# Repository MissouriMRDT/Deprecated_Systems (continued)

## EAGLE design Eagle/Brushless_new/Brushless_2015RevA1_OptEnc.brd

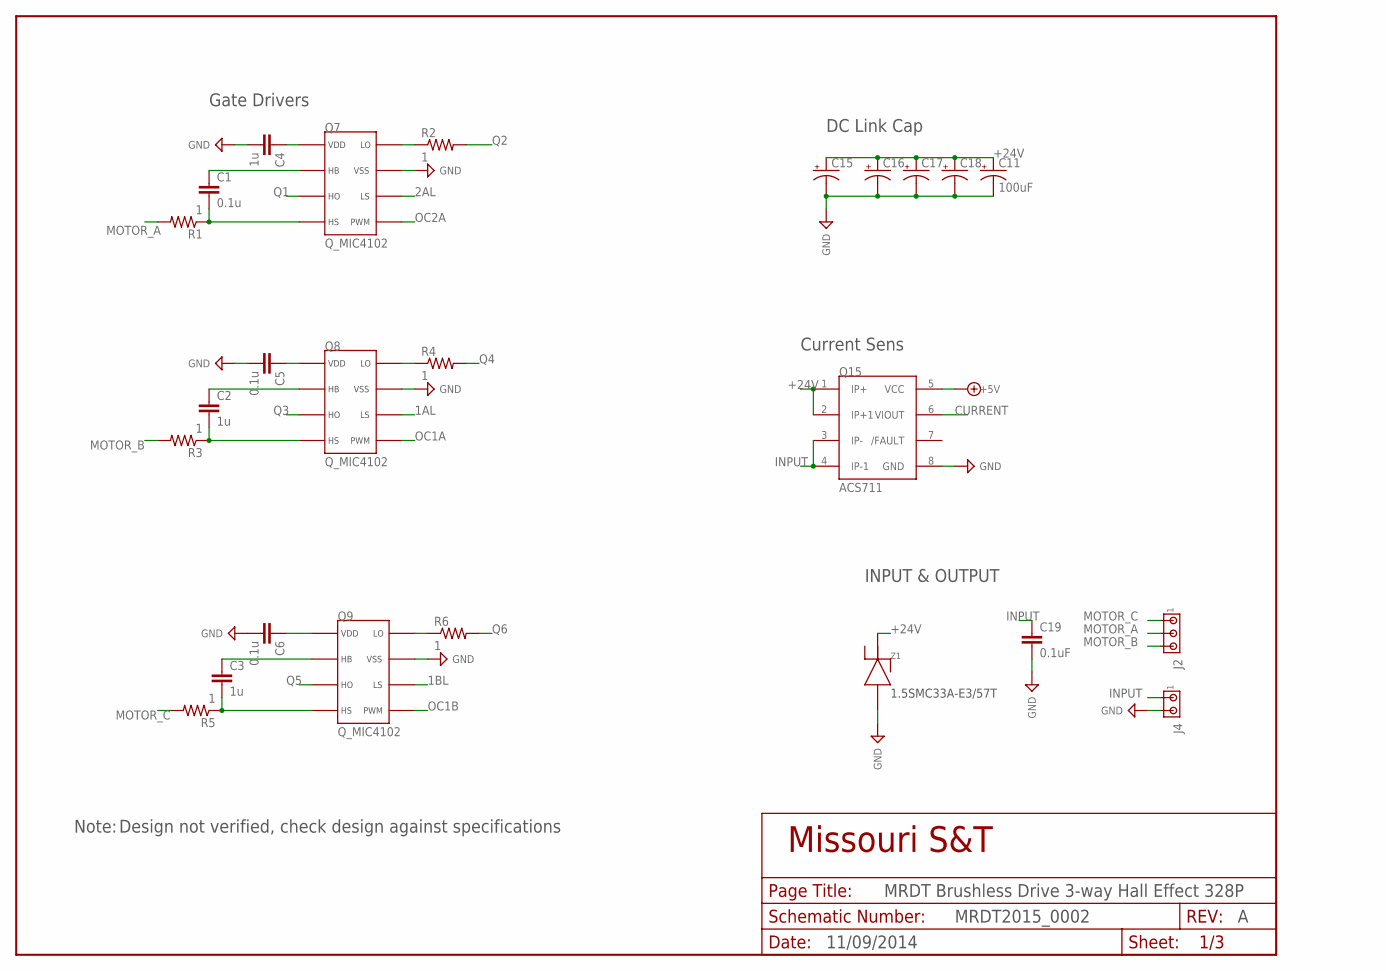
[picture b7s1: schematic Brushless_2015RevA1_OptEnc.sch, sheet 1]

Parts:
C1, C5, C6: 0.1u; C_1206
C2, C3, C4: 1u; C_1206
C11: 100uF; C_8MM
C15, C16, C17, C18: CAP_POL8MM; C_8MM
C19: 0.1uF; C_1206
J2: J_MTA3P_156; J_MTA156_3P
J4: J_HDR1X2_MTA_156MIL; J_MTA1X2_156MIL
Q7, Q8, Q9: Q_MIC4102; SOIC8
Q15: ACS711; SOIC8
R1, R2, R3, R4, R5, R6: 1; R_0805
Z1: Z_TVSDO214; DO-214AC

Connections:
1AL: Q8.6 (LS); also elsewhere on the board
1BL: Q9.6 (LS); also elsewhere on the board
2AL: Q7.6 (LS); also elsewhere on the board
+5V: Q15.5 (VCC); also elsewhere on the board
+12V: C4.1, C5.1, C6.1, Q7.1 (VDD), Q8.1 (VDD), Q9.1 (VDD); also elsewhere on the board
+24V: C11.+, C15.+, C16.+, C17.+, C18.+, Q15.1 (IP+), Q15.2 (IP+1), Z1.C; also elsewhere on the board
CURRENT: Q15.6 (VIOUT); also elsewhere on the board
GND: C4.2, C5.2, C6.2, C11.-, C15.-, C16.-, C17.-, C18.-, C19.2, J4.2, Q7.7 (VSS), Q8.7 (VSS), Q9.7 (VSS), Q15.8 (GND), Z1.A; also elsewhere on the board
INPUT: C19.1, J4.1, Q15.3 (IP-), Q15.4 (IP-1)
MOTOR_A: J2.2, R1.2; also elsewhere on the board
MOTOR_B: J2.3, R3.2; also elsewhere on the board
MOTOR_C: J2.1, R5.2; also elsewhere on the board
unnamed: Q7.8 (LO), R2.1
unnamed: Q8.8 (LO), R4.1
unnamed: Q9.8 (LO), R6.1
unnamed: C3.1, Q9.2 (HB)
unnamed: C3.2, Q9.4 (HS), R5.1
unnamed: C2.1, Q8.2 (HB)
unnamed: C2.2, Q8.4 (HS), R3.1
unnamed: C1.1, Q7.2 (HB)
unnamed: C1.2, Q7.4 (HS), R1.1
OC1A: Q8.5 (PWM); also elsewhere on the board
OC1B: Q9.5 (PWM); also elsewhere on the board
OC2A: Q7.5 (PWM); also elsewhere on the board
Q1: Q7.3 (HO); also elsewhere on the board
Q2: R2.2; also elsewhere on the board
Q3: Q8.3 (HO); also elsewhere on the board
Q4: R4.2; also elsewhere on the board
Q5: Q9.3 (HO); also elsewhere on the board
Q6: R6.2; also elsewhere on the board

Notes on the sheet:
1.5SMC33A-E3/57T
Gate Drivers
DC Link Cap
Current Sens
INPUT & OUTPUT
MRDT Brushless Drive 3-way Hall Effect 328P
MRDT2015_0002
11/09/2014
Note:
Design not verified, check design against specifications

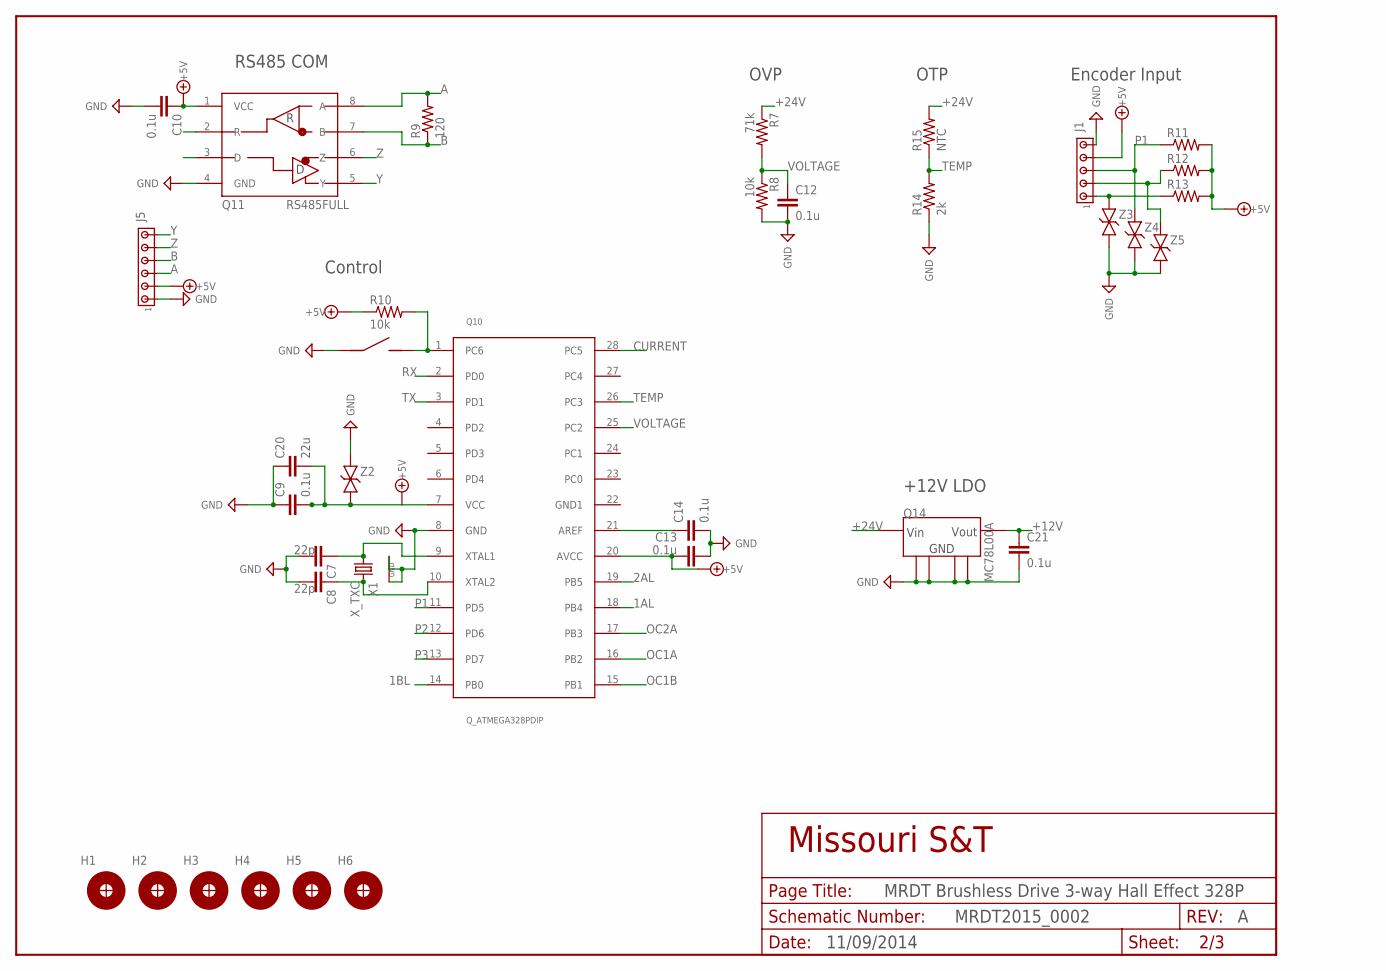
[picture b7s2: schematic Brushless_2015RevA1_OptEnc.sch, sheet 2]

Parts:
C7, C8: 22p; C_1206
C9, C10, C12, C13, C14, C21: 0.1u; C_0805
C20: 22u; C_1206
H1, H2, H3, H4, H5, H6: H_MNTHOLE_#4
J1: J_MTA5P_100; J_MTA100_5P
J3: J_MC32857; J_TOGGLE
J5: J_HDR1X6_MTA_100MIL; J_MTA1X6_100MIL
Q10: Q_ATMEGA328PDIP; DIP28
Q11: RS485FULL; SOIC8
Q14: MC78L00A; SOIC8
R7: 71k; R_0805
R8, R10: 10k; R_0805
R9: 120; R_0805
R11, R12, R13: R_RES_1206; R_1206
R14: 2k; R_0805
R15: NTC; R_0805
X1: X_TXC; SMD_CRYSTAL
Z2, Z3, Z4, Z5: Z_ESD0603; 0603

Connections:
1AL: Q10.18 (PB4); also elsewhere on the board
1BL: Q10.14 (PB0); also elsewhere on the board
2AL: Q10.19 (PB5); also elsewhere on the board
+5V: C9.2, C10.1, C13.1, C20.2, J1.4, J5.2, Q10.7 (VCC), Q10.20 (AVCC), Q11.1 (VCC), R10.1, R11.2, R12.2, R13.2, Z2.1; also elsewhere on the board
+12V: C21.1, Q14.1 (VOUT); also elsewhere on the board
+24V: Q14.8 (VIN), R7.1, R15.2; also elsewhere on the board
A: J5.3, Q11.8 (A), R9.2
B: J5.4, Q11.7 (B), R9.1
CURRENT: Q10.28 (PC5); also elsewhere on the board
GND: C7.2, C8.2, C9.1, C10.2, C12.2, C13.2, C14.2, C20.1, C21.2, J1.5, J3.P$1 (1), J5.1, Q10.8 (GND), Q11.4 (GND), Q14.2 (GND), Q14.3 (GND1), Q14.6 (GND3), Q14.7 (GND2), R8.2, R14.1, X1.2 (GND1), X1.4 (GND2), Z2.2, Z3.1, Z4.1, Z5.1; also elsewhere on the board
unnamed: J3.P$2 (2), Q10.1 (PC6), R10.2
unnamed: C7.1, Q10.9 (XTAL1), X1.1
unnamed: C8.1, Q10.10 (XTAL2), X1.3 (2)
unnamed: C14.1, Q10.21 (AREF)
OC1A: Q10.16 (PB2); also elsewhere on the board
OC1B: Q10.15 (PB1); also elsewhere on the board
OC2A: Q10.17 (PB3); also elsewhere on the board
P1: J1.3, Q10.11 (PD5), R11.1, Z4.2
P2: J1.2, Q10.12 (PD6), R12.1, Z5.2
P3: J1.1, Q10.13 (PD7), R13.1, Z3.2
RX: Q10.2 (PD0), Q11.2 (R)
TEMP: Q10.26 (PC3), R14.2, R15.1
TX: Q10.3 (PD1), Q11.3 (D)
VOLTAGE: C12.1, Q10.25 (PC2), R7.2, R8.1
Y: J5.6, Q11.5 (Y)
Z: J5.5, Q11.6 (Z)

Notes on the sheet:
RS485 COM
Control
Encoder Input
OTP
OVP
+12V LDO
MRDT Brushless Drive 3-way Hall Effect 328P
MRDT2015_0002
11/09/2014

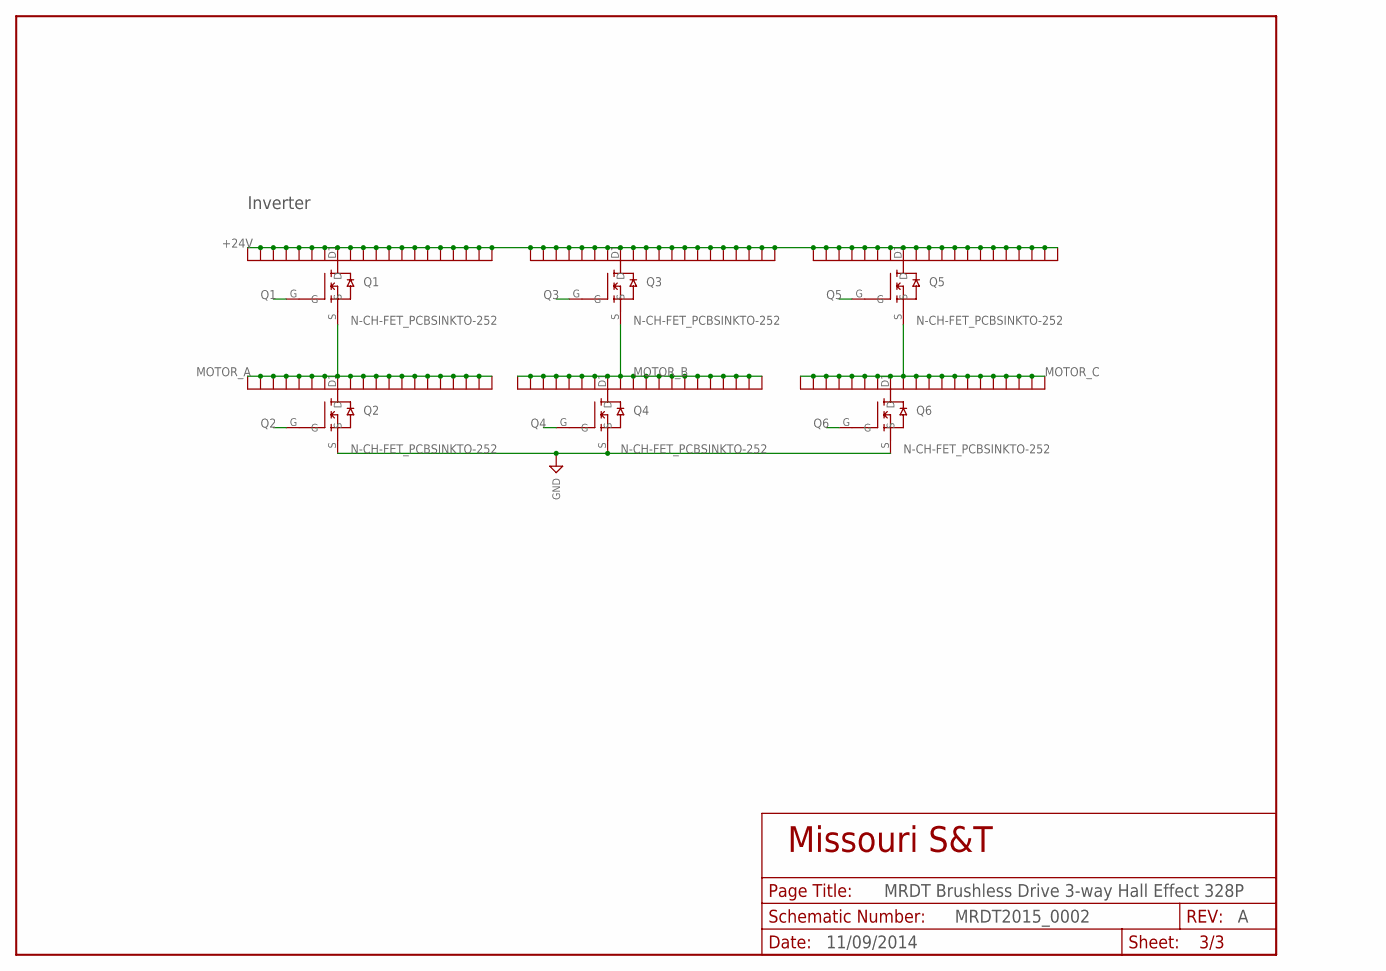
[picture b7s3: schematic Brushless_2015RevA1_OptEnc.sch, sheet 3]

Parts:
Q1, Q2, Q3, Q4, Q5, Q6: N-CH-FET_PCBSINKTO-252; TO-252-SINK

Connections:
+24V: Q1.D1 (D), Q1.D2, Q1.D3, Q1.D4, Q1.D5, Q1.D6, Q1.D7, Q1.D8, Q1.D9, Q1.D10, Q1.D11, Q1.D12, Q1.D13, Q1.D14, Q1.D15, Q1.D16, Q1.D17, Q1.D18, Q1.D19, Q1.D20, Q3.D1 (D), Q3.D2, Q3.D3, Q3.D4, Q3.D5, Q3.D6, Q3.D7, Q3.D8, Q3.D9, Q3.D10, Q3.D11, Q3.D12, Q3.D13, Q3.D14, Q3.D15, Q3.D16, Q3.D17, Q3.D18, Q3.D19, Q3.D20, Q5.D1 (D), Q5.D2, Q5.D3, Q5.D4, Q5.D5, Q5.D6, Q5.D7, Q5.D8, Q5.D9, Q5.D10, Q5.D11, Q5.D12, Q5.D13, Q5.D14, Q5.D15, Q5.D16, Q5.D17, Q5.D18, Q5.D19, Q5.D20; also elsewhere on the board
GND: Q2.S, Q4.S, Q6.S; also elsewhere on the board
MOTOR_A: Q1.S, Q2.D1 (D), Q2.D2, Q2.D3, Q2.D4, Q2.D5, Q2.D6, Q2.D7, Q2.D8, Q2.D9, Q2.D10, Q2.D11, Q2.D12, Q2.D13, Q2.D14, Q2.D15, Q2.D16, Q2.D17, Q2.D18, Q2.D19, Q2.D20; also elsewhere on the board
MOTOR_B: Q3.S, Q4.D1 (D), Q4.D2, Q4.D3, Q4.D4, Q4.D5, Q4.D6, Q4.D7, Q4.D8, Q4.D9, Q4.D10, Q4.D11, Q4.D12, Q4.D13, Q4.D14, Q4.D15, Q4.D16, Q4.D17, Q4.D18, Q4.D19, Q4.D20; also elsewhere on the board
MOTOR_C: Q5.S, Q6.D1 (D), Q6.D2, Q6.D3, Q6.D4, Q6.D5, Q6.D6, Q6.D7, Q6.D8, Q6.D9, Q6.D10, Q6.D11, Q6.D12, Q6.D13, Q6.D14, Q6.D15, Q6.D16, Q6.D17, Q6.D18, Q6.D19, Q6.D20; also elsewhere on the board
Q1: Q1.G; also elsewhere on the board
Q2: Q2.G; also elsewhere on the board
Q3: Q3.G; also elsewhere on the board
Q4: Q4.G; also elsewhere on the board
Q5: Q5.G; also elsewhere on the board
Q6: Q6.G; also elsewhere on the board

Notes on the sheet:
Inverter
MRDT Brushless Drive 3-way Hall Effect 328P
MRDT2015_0002
11/09/2014

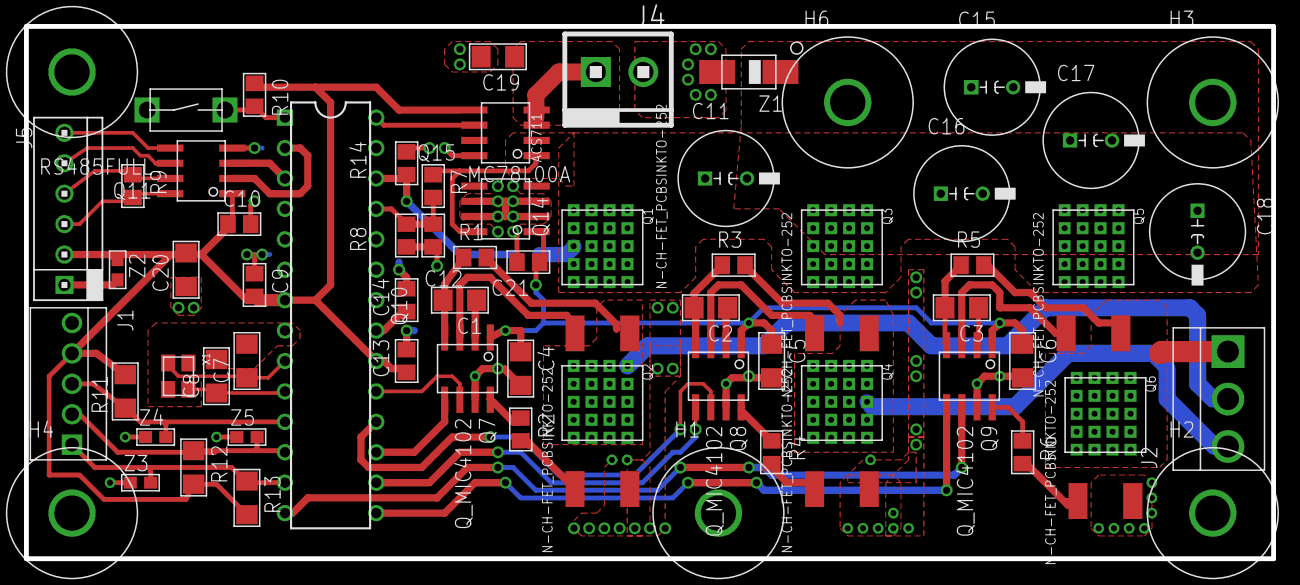
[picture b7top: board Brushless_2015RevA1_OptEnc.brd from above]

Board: 2 copper layers, 104.1 x 44.5 mm, 66 parts (1 on the bottom side), 45 nets.
